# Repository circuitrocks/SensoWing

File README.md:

# Circuitrocks SensoWing

Want to make a quick prototype with some sensors and your Feather boards? Then you might stumble over the same problem we did. 
The Feather system is great as long as you only need to put some Feathers and some Wings together. But how do you connect your sensors, actuators or display?
Well, you can buy a FeatherWing proto board, solder connectors and wires to it and plug your sensors, actuators or display in. But wait, what if your sensor is one of the Sparkfun sensors with a QUICC connector? Good luck with soldering the 1mm pitch QUICC connector to a prototype board.

Don't worry anymore, all these struggles made us think that a Feather with connectors is a good idea.
Our SensoWing has 5 connectors, already wired to the standard I2C, SPI, Serial and Analog ports of the Feathers.
SensoWing carries
- one QUICC connector with I2C
- one Grove connector with I2C
- one Grove connector with Serial
- one Grove connector with 2 Analog inputs or outputs
- one header for SPI bus with the option to connect the SPI CS to any of the free GPIOs.

Sounds good?
What are you waiting for, order some of them, you will find them handy.
If you have some other sensors or stuff without Grove or QUICC connector, don't worry, we have as well some Grove cables in stock that you can solder to your sensors and just plug them into the SensoWing.

The SensoWing comes without headers soldered to it, so you can solder your own choice of headers to it.

## Applications:
Quick prototyping.

## Specifications:
- 1 x 1mm pitch I2C connector compatible with Sparkfuns QUICC standard.
- 1 x I2C connector compatible with Seeed Studio Grove standard.
- 1 x Serial connecter compatible with Seeed Studio Grove standard.
- 1 x Analog in or out connector compatible with Seeed Studio Grove standard.
- 1 x header with SPI bus
- SPI chip select connected to any available GPIO by putting a simple solder bridge

## Technical details:
EagleCAD PCB files, datasheets and more on Github    
Dimensions 2.0”x0.9”x0.28” (51mmx23mmx8mm)

[Check out our tutorial for pinouts and some tips how to use the SensoWing.](https://learn.circuit.rocks/circuitrocks-sensowing)

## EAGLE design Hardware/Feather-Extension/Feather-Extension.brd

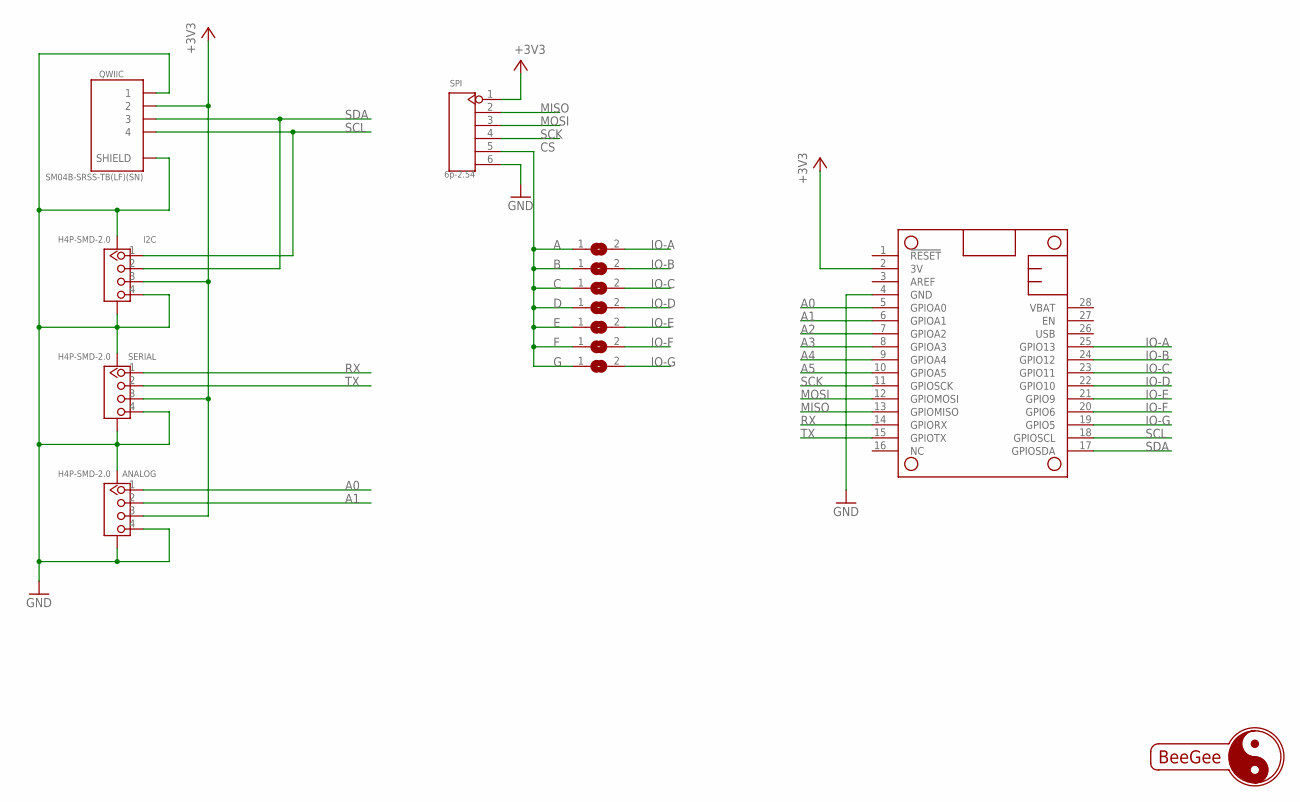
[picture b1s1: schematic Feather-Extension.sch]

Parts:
A: SJ
ANALOG: H4P-SMD-2.0; HW4-SMD-2.0
B: SJ
C: SJ
D: SJ
E: SJ
F: SJ
G: SJ
I2C: H4P-SMD-2.0; HW4-SMD-2.0
MS2: FEATHERWING
QWIIC: SM04B-SRSS-TB(LF)(SN); JST_SM04B-SRSS-TB(LF)(SN)
SERIAL: H4P-SMD-2.0; HW4-SMD-2.0
SPI: 6p-2.54; H6-2.54

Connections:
+3V3: ANALOG.3, I2C.3, MS2.2 (3V), QWIIC.2, SERIAL.3, SPI.1
A0: ANALOG.1, MS2.5 (GPIOA0)
A1: ANALOG.2, MS2.6 (GPIOA1)
A2: MS2.7 (GPIOA2)
A3: MS2.8 (GPIOA3)
A4: MS2.9 (GPIOA4)
A5: MS2.10 (GPIOA5)
CS: A.1, B.1, C.1, D.1, E.1, F.1, G.1, SPI.5
GND: ANALOG.4, ANALOG.SS1, ANALOG.SS2, I2C.4, I2C.SS1, I2C.SS2, MS2.4 (GND), QWIIC.1, QWIIC.S1 (SHIELD), QWIIC.S2 (SHIELD), SERIAL.4, SERIAL.SS1, SERIAL.SS2, SPI.6
IO-A: A.2, MS2.25 (GPIO13)
IO-B: B.2, MS2.24 (GPIO12)
IO-C: C.2, MS2.23 (GPIO11)
IO-D: D.2, MS2.22 (GPIO10)
IO-E: E.2, MS2.21 (GPIO9)
IO-F: F.2, MS2.20 (GPIO6)
IO-G: G.2, MS2.19 (GPIO5)
MISO: MS2.13 (GPIOMISO), SPI.2
MOSI: MS2.12 (GPIOMOSI), SPI.3
RX: MS2.14 (GPIORX), SERIAL.1
SCK: MS2.11 (GPIOSCK), SPI.4
SCL: I2C.1, MS2.18 (GPIOSCL), QWIIC.4
SDA: I2C.2, MS2.17 (GPIOSDA), QWIIC.3
TX: MS2.15 (GPIOTX), SERIAL.2

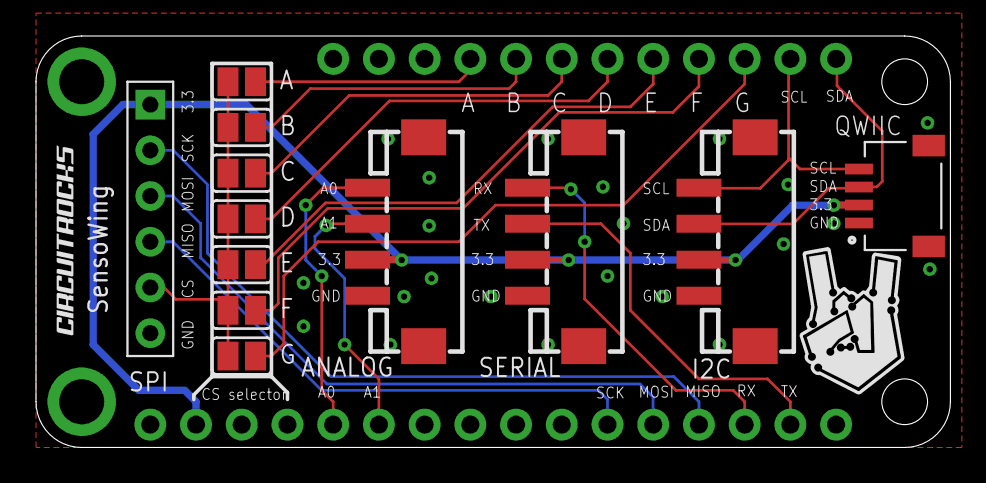
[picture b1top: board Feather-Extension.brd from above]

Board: 2 copper layers, 50.8 x 22.9 mm, 13 parts (0 on the bottom side), 19 nets.

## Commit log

2019-12-10 Added content
2019-12-10 Corrected Readme
